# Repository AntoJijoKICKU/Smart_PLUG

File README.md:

# Smart_PLUG
This is Untested version of Hardware Double check your Everything before take this as reference

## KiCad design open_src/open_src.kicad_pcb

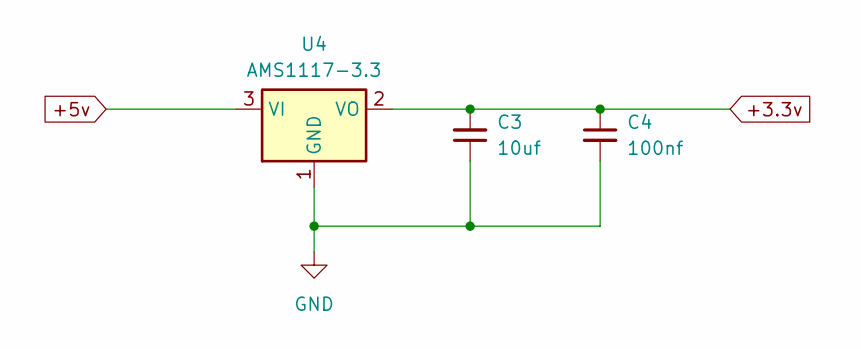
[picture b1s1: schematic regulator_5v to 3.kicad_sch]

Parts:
C3: 10uf; C_0201_0603Metric
C4: 100nf; C_0201_0603Metric
U4: AMS1117-3.3; SOT-223-3_TabPin2

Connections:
+3.3v: C3.2, C4.1, U4.2 (VO); also elsewhere on the board
+5v: U4.3 (VI); also elsewhere on the board

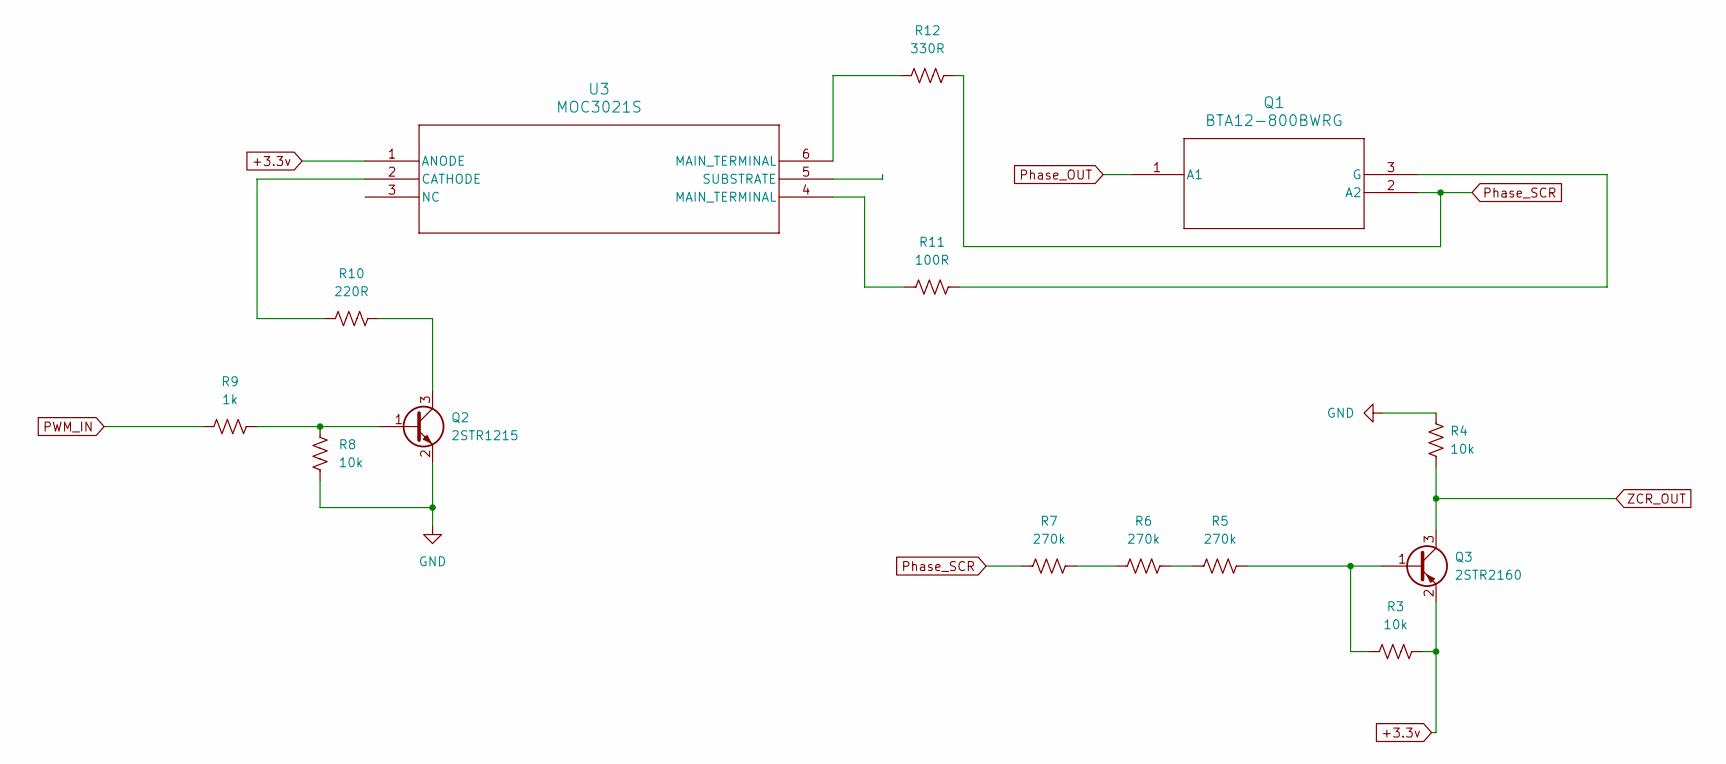
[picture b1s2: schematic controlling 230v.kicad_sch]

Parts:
Q1: BTA12-800BWRG; TO-220-3_Vertical
Q2: 2STR1215; SOT-23
Q3: 2STR2160; SOT-23
R3, R4: 10k; R_0402_1005Metric
R5, R6, R7: 270k; R_1206_3216Metric
R8: 10k; R_0201_0603Metric
R9: 1k; R_0201_0603Metric
R10: 220R; R_0402_1005Metric
R11: 100R; R_1206_3216Metric
R12: 330R; R_1206_3216Metric
U3: MOC3021S; MOC3021S_LTO

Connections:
+3.3v: Q3.2 (E), R3.2, U3.1 (ANODE); also elsewhere on the board
unnamed: Q1.3 (G), R11.2
unnamed: Q2.1 (B), R8.2, R9.1
unnamed: Q2.3 (C), R10.1
unnamed: Q3.1 (B), R3.1, R5.2
unnamed: R5.1, R6.2
unnamed: R6.1, R7.2
unnamed: R11.1, U3.4 (MAIN_TERMINAL)
unnamed: R12.1, U3.6 (MAIN_TERMINAL)
unnamed: R10.2, U3.2 (CATHODE)
PWM_IN: R9.2; also elsewhere on the board
Phase_OUT: Q1.1 (A1); also elsewhere on the board
Phase_SCR: Q1.2 (A2), R7.1, R12.2; also elsewhere on the board
ZCR_OUT: Q3.3 (C), R4.2; also elsewhere on the board

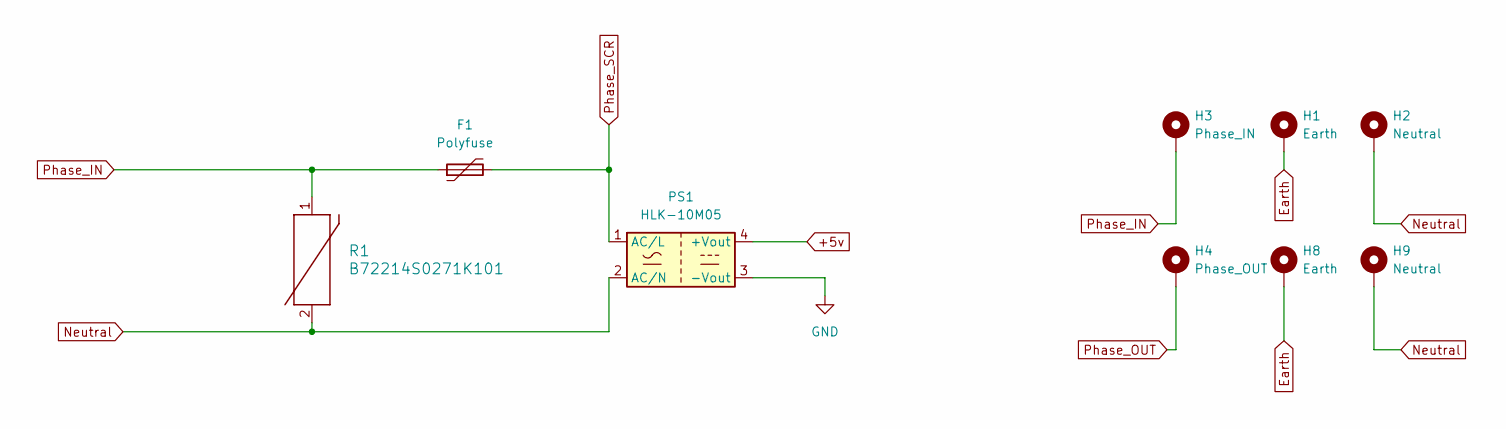
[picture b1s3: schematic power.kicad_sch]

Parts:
F1: Polyfuse; Fuseholder_Cylinder-5x20mm_Schurter_OGN-SMD_Horizontal_Open
H1, H8: Earth; MountingHole_8.4mm_M8_Pad
H2, H9: Neutral; MountingHole_8.4mm_M8_Pad
H3: Phase_IN; MountingHole_8.4mm_M8_Pad
H4: Phase_OUT; MountingHole_8.4mm_M8_Pad
PS1: HLK-10M05; Converter_ACDC_HiLink_HLK-10Mxx
R1: B72214S0271K101; VARS_B72214S0271K101_TDK

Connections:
+5v: PS1.4 (+Vout); also elsewhere on the board
Earth: H1.1, H8.1
Neutral: H2.1, H9.1, PS1.2 (AC/N), R1.2; also elsewhere on the board
Phase_IN: F1.1, H3.1, R1.1
Phase_OUT: H4.1; also elsewhere on the board
Phase_SCR: F1.2, PS1.1 (AC/L); also elsewhere on the board

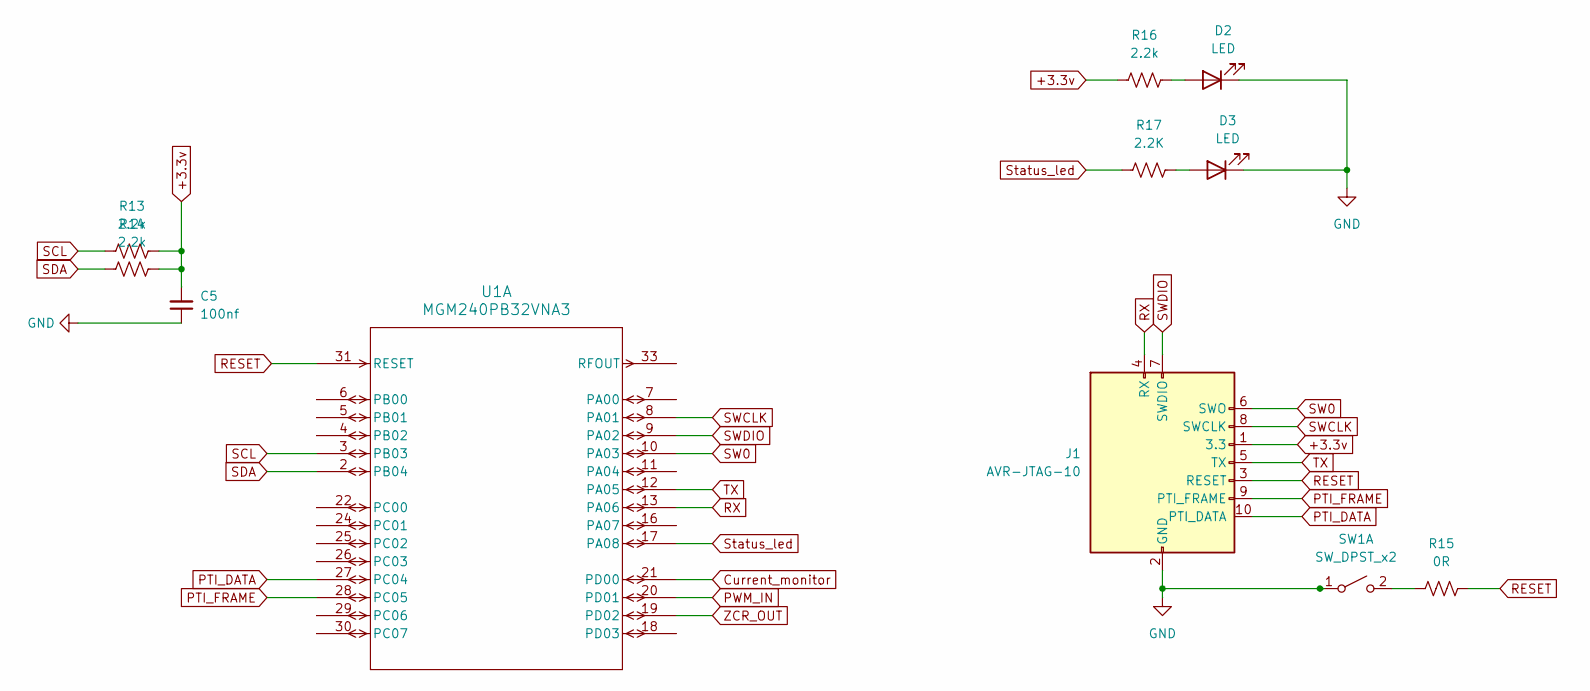
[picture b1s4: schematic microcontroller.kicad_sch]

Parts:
C5: 100nf; C_01005_0402Metric
D2, D3: LED; LED_0402_1005Metric
J1: AVR-JTAG-10; PinHeader_2x05_P1.27mm_Vertical_SMD
R13, R14, R16: 2.2k; R_0402_1005Metric
R15: 0R; R_0402_1005Metric
R17: 2.2K; R_0402_1005Metric
SW1: SW_DPST_x2; SW_Tactile_SPST_NO_Straight_CK_PTS636Sx25SMTRLFS
U1: MGM240PB32VNA3; xGM240P

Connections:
+3.3v: C5.2, J1.1 (3.3), R13.2, R14.2, R16.1, U1.15 (VDD); also elsewhere on the board
Current_monitor: U1.21 (PD00); also elsewhere on the board
unnamed: D2.2 (A), R16.2
unnamed: D3.2 (A), R17.2
unnamed: R15.1, SW1.2 (B)
PTI_FRAME: J1.9 (PTI_FRAME), U1.28 (PC05)
PWM_IN: U1.20 (PD01); also elsewhere on the board
RESET: J1.3 (RESET), R15.2, U1.31 (RESET)
RX: J1.4 (RX), U1.13 (PA06)
SCL: R13.1, U1.3 (PB03)
SDA: R14.1, U1.2 (PB04)
SW0: J1.6 (SWO), U1.10 (PA03)
SWCLK: J1.8 (SWCLK), U1.8 (PA01)
SWDIO: J1.7 (SWDIO), U1.9 (PA02)
Status_led: R17.1, U1.17 (PA08)
TX: J1.5 (TX), U1.12 (PA05)
ZCR_OUT: U1.19 (PD02); also elsewhere on the board

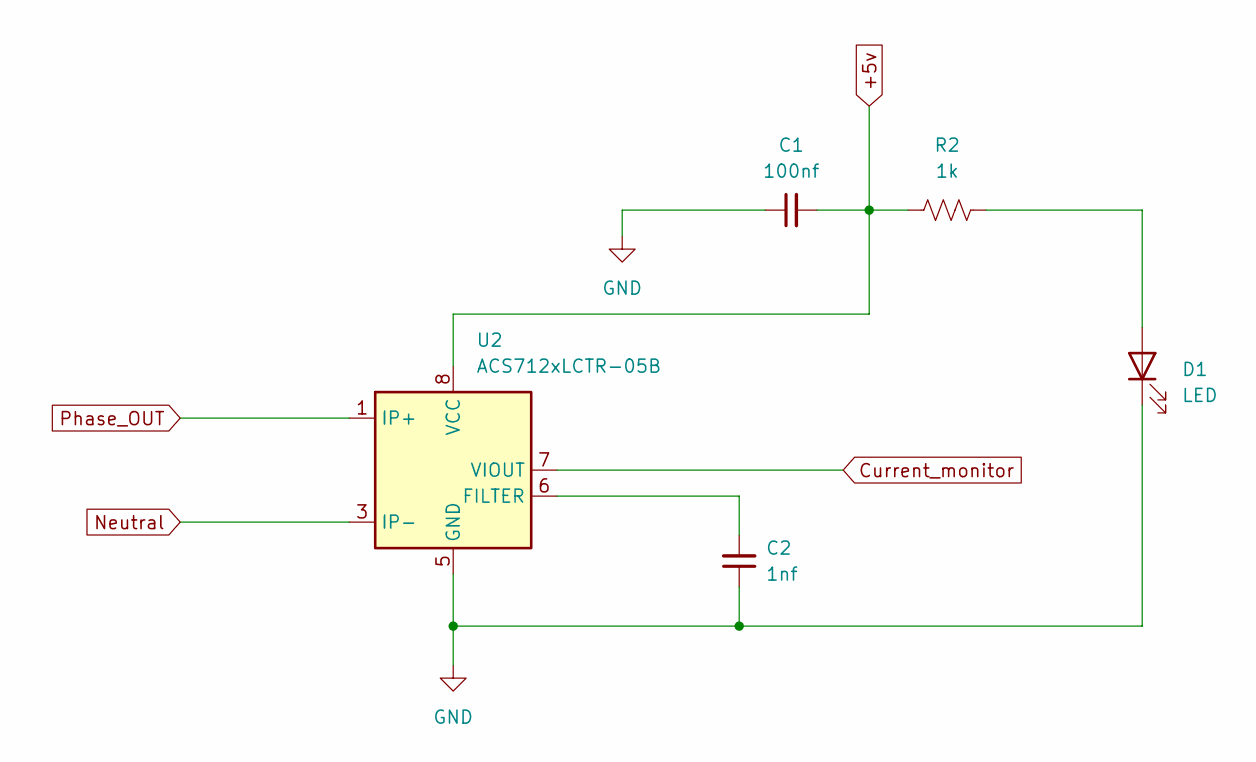
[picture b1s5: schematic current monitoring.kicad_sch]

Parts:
C1: 100nf; C_01005_0402Metric
C2: 1nf; C_01005_0402Metric
D1: LED; LED_0402_1005Metric
R2: 1k; R_0402_1005Metric
U2: ACS712xLCTR-05B; SOIC-8_3.9x4.9mm_P1.27mm

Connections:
+5v: C1.2, R2.1, U2.8 (VCC); also elsewhere on the board
Current_monitor: U2.7 (VIOUT); also elsewhere on the board
unnamed: D1.2 (A), R2.2
unnamed: C2.2, U2.6 (FILTER)
Neutral: U2.3 (IP-), U2.4 (IP-); also elsewhere on the board
Phase_OUT: U2.1 (IP+), U2.2 (IP+); also elsewhere on the board

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
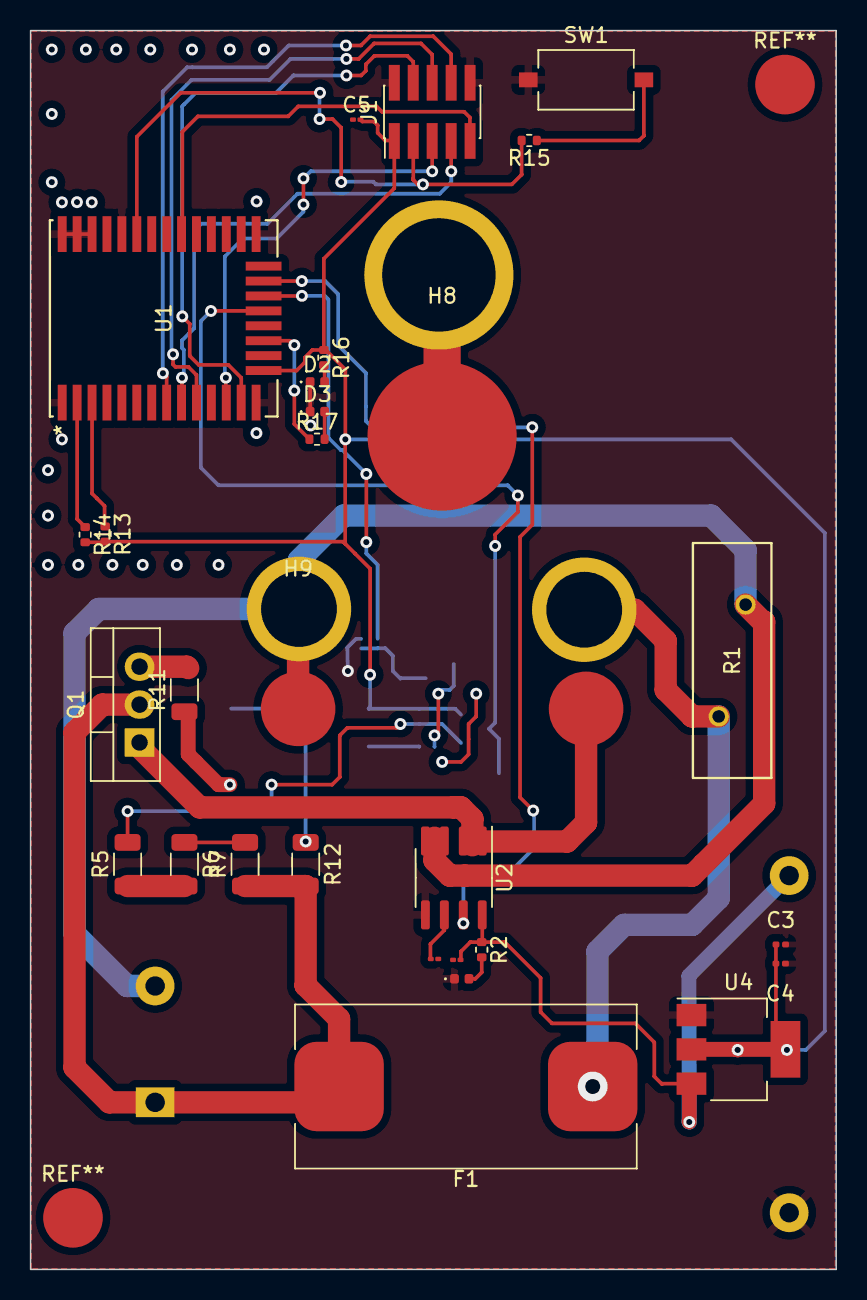
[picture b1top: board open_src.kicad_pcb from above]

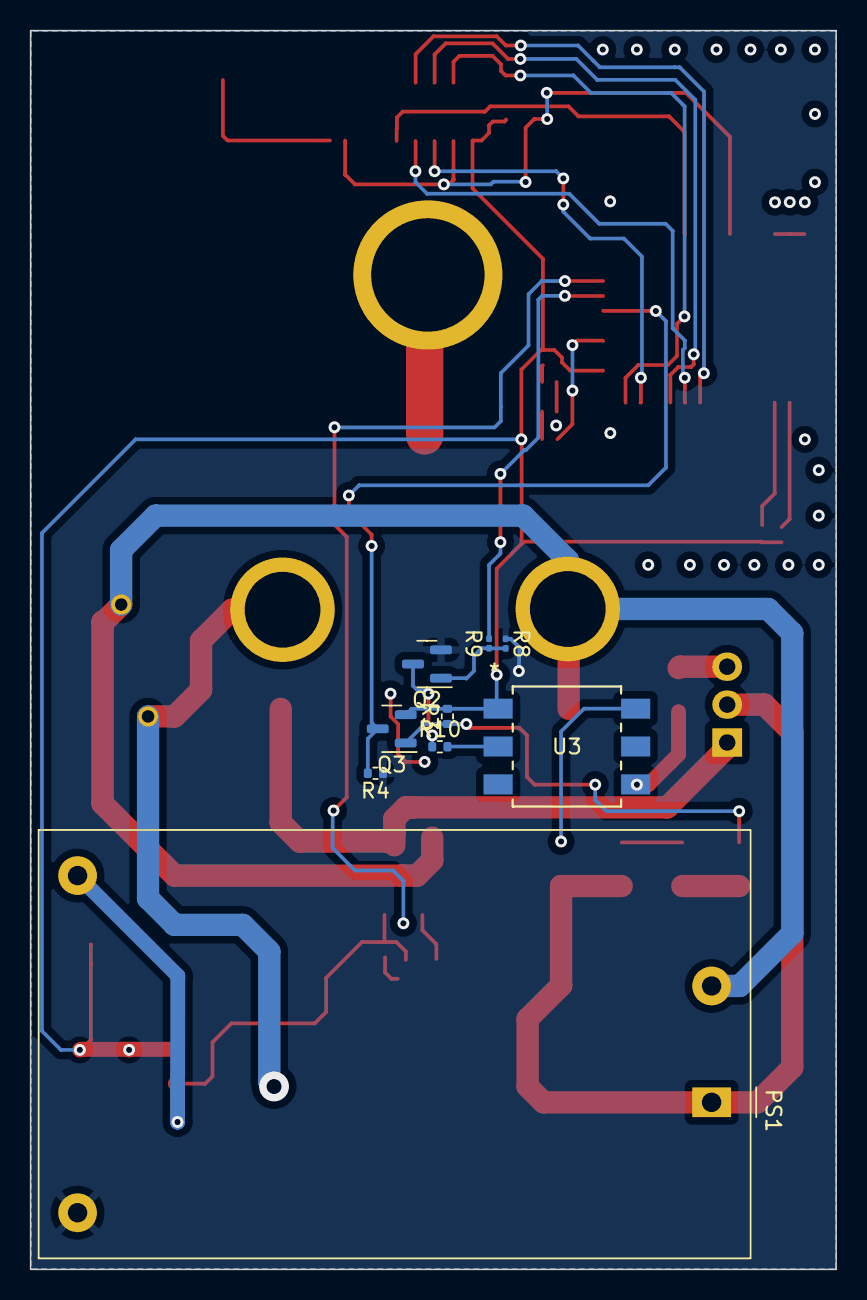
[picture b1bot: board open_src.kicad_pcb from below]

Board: 2 copper layers, 54.0 x 83.0 mm, 42 parts (9 on the bottom side), 35 nets.

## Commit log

2024-01-16 Initial commit without tracks
2024-01-16 Added trace
    Still not yet cross checked
2024-01-16 Gerbers and schematics added
2024-01-16 pcb pictures addded
